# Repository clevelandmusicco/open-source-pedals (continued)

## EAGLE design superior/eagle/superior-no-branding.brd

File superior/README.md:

# Superior Overdrive

The [Superior Overdrive](https://clevelandmusicco.com/pedals/superior-overdrive/) is a 2-in-1 powerhouse pedal packed with our EastSide Overdrive stacked into the WestSide Overdrive. This combination of transparent low- and medium-gain drives, with all their tone and clipping options, is a remarkably flexible dirt platform.

There are 3 interdependent PCBs in this pedal's design.

## The Effect PCB

[Tayda Enclosure Drill Template](https://drill.taydakits.com/box-designs/new?public_key=SVhxKzdDNXZjeXVUNXpSM1phNTFkdz09Cg==)

### Through-hole Component Suggestions

Coming soon.

## The I/O PCB

Coming soon.

## The Filtering & Switching PCB

Coming soon.

## Marketing blurb from our official web site

### A space-saving, rugged, and enormously versatile overdrive platform at an affordable price.

The Cleveland Music Co. Superior Overdrive is a 2-in-1 pedal packed with 2 of our most popular overdrives, and they happen to stack extremely well. Use them individually, set them both to detonate, or dial one in as a boost to help you cut through the mix. These two circuits stacked like this is just glorious; better than any other combination we’ve played. That’s why it’s called the Superior Overdrive.

#### EastSide Overdrive (first in the signal chain)
The Cleveland Music Co. EastSide Overdrive is our love letter to the pinnacle of transparent, boutique overdrives: the Timmy. Its low- to medium-gain tones can be dialed in for anything from a powerful, dirty boost for stacking with other pedals, to flat out rock-n-roll grind. With a potent EQ section and plenty of output volume to spare, the EastSide can easily push an on-the-edge amplifier’s tubes into overdrive territory.

* **VOLUME:** Sets the overall output volume. There is quite a lot of output on tap, which makes the EastSide a great boost option for stacking with other overdrives, or slamming the front of your favorite tube amp.
* **GAIN:** Clockwise for more gain; counter-clockwise for less. While there is a little more gain available than typical transparent overdrives, the EastSide is still a medium-gain pedal. Pro tip: putting a boost or another drive in front of the EastSide can push it into high-gain bliss!
* **TREBLE:** Works like you would expect: adds or cuts treble. Clockwise for more; counter-clockwise for less.
* **BASS:** Adds or cuts bass. Clockwise for more; counter-clockwise for less.
* **COMP | SYM | ASYM:** Selects between three clipping options:
 * Compressed aggressively clips the signal, producing a rich, saturated overdrive tone. This is the least transparent setting.
 * Symmetrical clips the peaks and valleys of the signal equally, resulting in a smooth, sustained overdrive tone.
 * Asymmetrical clips the waveform unequally, creating a more open tone.

The EastSide features an internal trimmer that allows you to fine-tune the bass frequencies prior to the distortion stage of the circuit. Great for “hot” humbuckers that tend to overpower typical overdrives.

#### WestSide Overdrive (second in the signal chain)

The Cleveland Music Co. WestSide Overdrive is inspired by the classic Blues Breaker—both the amp and the pedal. After poring over the schematics of the original JTM 45 amplifier, the original pedal, and many pedals based on both, we applied what we feel are the strengths of them all into the WestSide. Not content to be a rehash of the past, the WestSide offers additional tonal and clipping options, increased output volume, and the powerful presence control makes it feel at home in any rig. The result is a touch-sensitive, bluesy, low-gain overdrive that stacks especially well with our other low- to medium-gain drives, and gives you all the presence you need to stand out.

* **VOLUME:** Sets the overall output volume. Unity gain is around 2 o’clock, so the classic “low-gain, high-volume” configuration can really push the front of a tube amp with the volume cranked.
* **GAIN:** Clockwise for more gain; counter-clockwise for less. There is a little more gain available than from typical pedals of this style, so be brave and explore. But for those looking for the so-called traditional sweet spots, try the 9 o’clock to noon range.
* **PRESENCE:** Sets the amount of Presence. Fully counter-clockwise for most rigs (start here!); clockwise to brighten up a dark amp or guitar pickups.
* **TONE:** Clockwise for more treble; counter-clockwise for less.
* **COMP | OPEN:**
 * Compressed is the traditional clipping option for this style pedal, producing a rich, saturated overdrive tone.
 * Open inserts LEDs as the clipping diodes, resulting in a brighter, louder, and more open sound.

True-bypass switching. Jacks and power are on the top to save space on your pedalboard, and the pedal is industry-standard 1590BB size (4.7 in x 3.7 in x 2.5 in, including knobs).

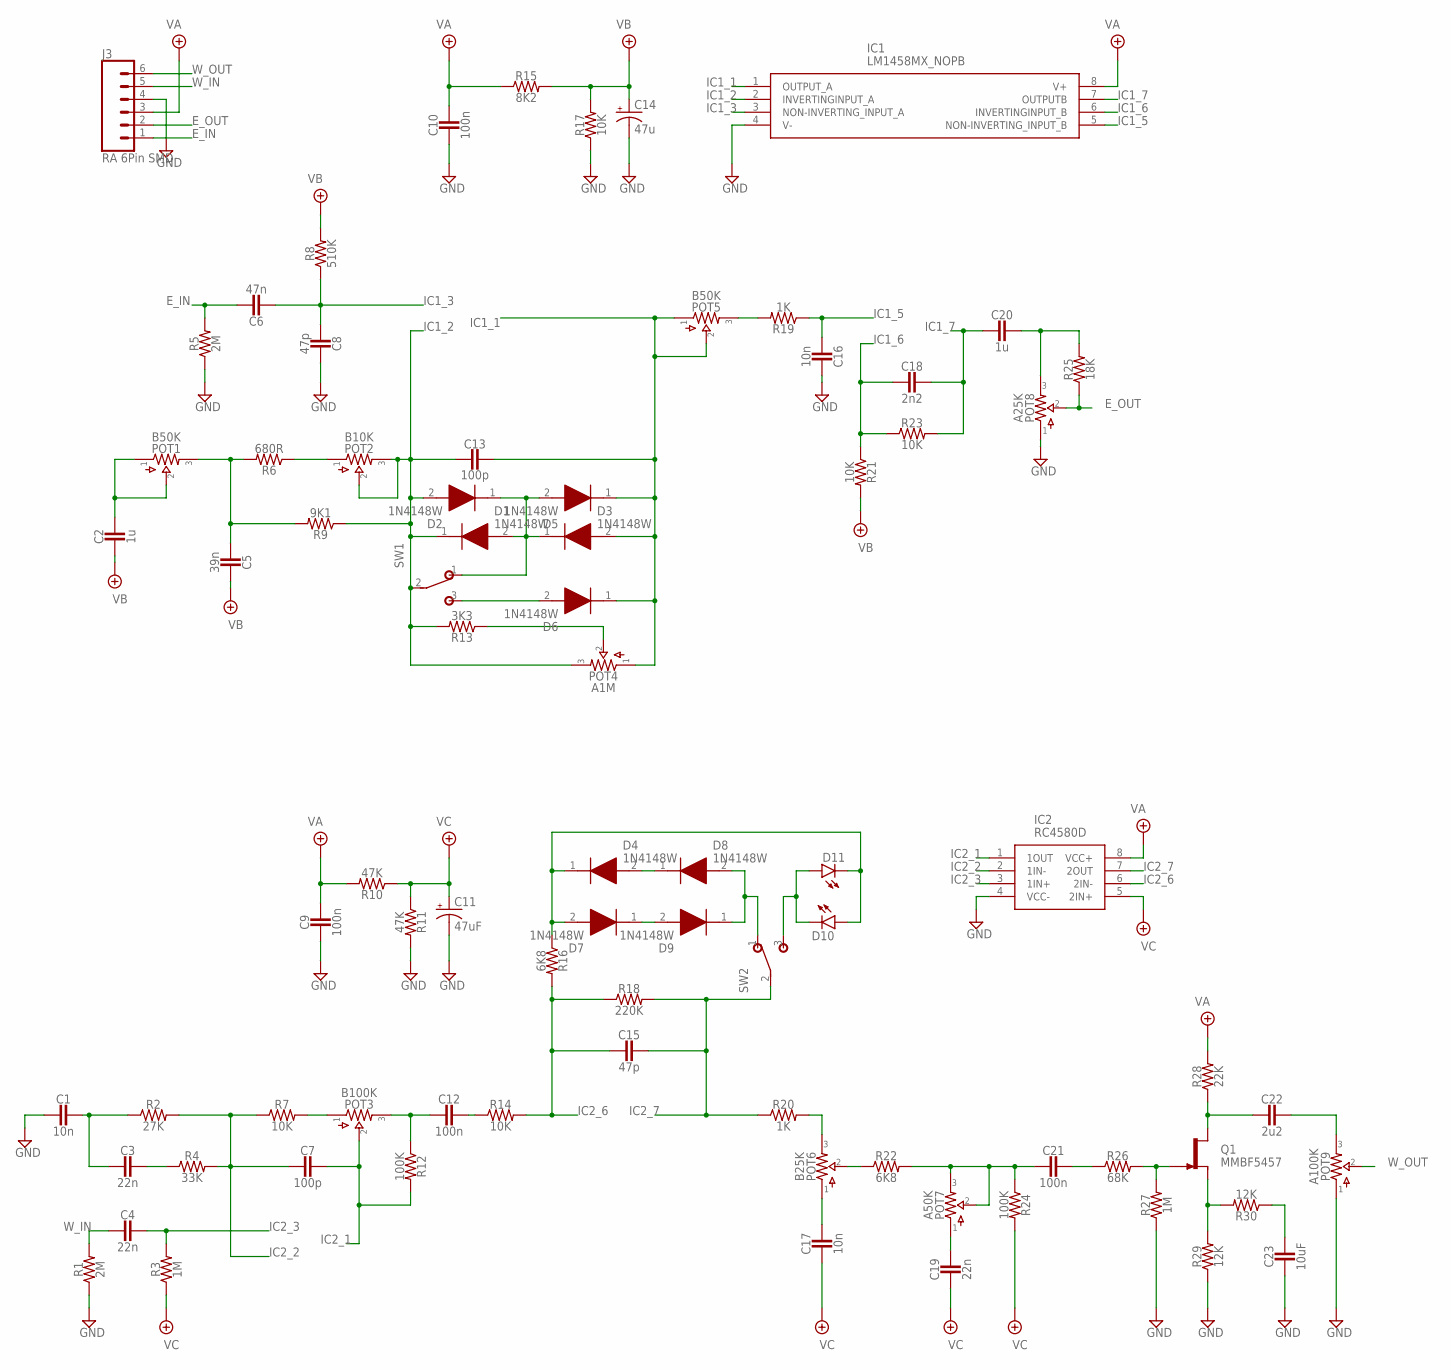
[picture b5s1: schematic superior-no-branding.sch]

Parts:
C1, C16, C17: 10n; 0603
C2: 1u; 0805
C3, C19: 22n; 0603
C4: 22n; 0805
C5: 39n; 0603
C6: 47n; 1206
C7: 100p; 0603
C8, C15: 47p; 0603
C9, C10: 100n; 0603
C11: 47uF; 050_020_1
C12, C21: 100n; 1206
C13: 100p; 0.2".MED
C14: 47u; 050_020_1
C18: 2n2; 0603
C20: 1u; 1206
C22: 2u2; 1206
C23: 10uF; 1206
D1, D2, D3, D4, D5, D6, D7, D8, D9: 1N4148W; SODFL3816X120N
D10, D11: LED3MM
IC1: LM1458MX_NOPB; SOIC127P600X175-8N
IC2: RC4580D; SOIC127P600X175-8N
J3: RA 6Pin SMD; 1X06
POT1, POT5: B50K; 16MM_B.MOUNT
POT2: B10K; TRIM1
POT3: B100K; 16MM_B.MOUNT
POT4: A1M; 16MM_B.MOUNT
POT6: B25K; 16MM_B.MOUNT
POT7: A50K; 16MM_B.MOUNT
POT8: A25K; 16MM_B.MOUNT
POT9: A100K; 16MM_B.MOUNT
Q1: MMBF5457; SOT23-DGS
R1, R5: 2M; 0603
R2: 27K; 0603
R3, R27: 1M; 0603
R4: 33K; 0603
R6: 680R; 0603
R7, R14, R17, R21, R23: 10K; 0603
R8: 510K; 0603
R9: 9K1; 0603
R10, R11: 47K; 0603
R12, R24: 100K; 0603
R13: 3K3; 0603
R15: 8K2; 0603
R16, R22: 6K8; 0603
R18: 220K; 0603
R19, R20: 1K; 0603
R25: 18K; 0603
R26: 68K; 0603
R28: 22K; 0603
R29, R30: 12K; 0603
SW1, SW2: SPDT; M9040P

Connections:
E_IN: C6.1, J3.1, R5.2
E_OUT: J3.2, POT8.2, R25.1
GND: C1.2, C8.1, C9.2, C10.2, C11.-, C14.-, C16.1, C23.2, IC1.4 (V-), IC2.4 (VCC-), J3.4, POT8.1, POT9.1, R1.1, R5.1, R11.2, R17.1, R27.1, R29.1
IC1_1: C13.1, D3.2 (A), D5.1 (K), D6.1 (K), IC1.1 (OUTPUT_A), POT4.1, POT5.1, POT5.2
IC1_2: C13.2, D1.1 (K), D2.2 (A), IC1.2 (INVERTINGINPUT_A), POT2.2, POT2.3, POT4.3, R9.1, R13.2, SW1.2
IC1_3: C6.2, C8.2, IC1.3 (NON-INVERTING_INPUT_A), R8.1
IC1_5: C16.2, IC1.5 (NON-INVERTING_INPUT_B), R19.1
IC1_6: C18.2, IC1.6 (INVERTINGINPUT_B), R21.1, R23.1
IC1_7: C18.1, C20.2, IC1.7 (OUTPUTB), R23.2
IC2_1: C7.1, IC2.1 (1OUT), POT3.2, R12.2
IC2_2: C7.2, IC2.2 (1IN-), R2.2, R4.2, R7.1
IC2_3: C4.1, IC2.3 (1IN+), R3.2
IC2_6: C15.2, IC2.6 (2IN-), R14.2, R16.2, R18.1
IC2_7: C15.1, IC2.7 (2OUT), R18.2, R20.1, SW2.2
unnamed: C5.2, POT1.3, R6.2, R9.2
unnamed: POT4.2, R13.1
unnamed: C2.1, POT1.1, POT1.2
unnamed: POT2.1, R6.1
unnamed: D1.2 (A), D2.1 (K), D3.1 (K), D5.2 (A), SW1.1 (O)
unnamed: D6.2 (A), SW1.3 (S)
unnamed: C3.1, R4.1
unnamed: POT5.3, R19.2
unnamed: C1.1, C3.2, R2.1
unnamed: C12.2, POT3.3, R12.1
unnamed: C20.1, POT8.3, R25.2
unnamed: C12.1, R14.1
unnamed: D4.1 (K), D7.2 (A), D10.A, D11.K (C), R16.1
unnamed: D4.2 (A), D8.1 (K)
unnamed: D7.1 (K), D9.2 (A)
unnamed: POT6.3, R20.2
unnamed: POT6.2, R22.1
unnamed: C17.1, POT6.1
unnamed: C21.2, POT7.2, POT7.3, R22.2, R24.1
unnamed: C21.1, R26.1
unnamed: Q1.G, R26.2, R27.2
unnamed: Q1.S, R29.2, R30.2
unnamed: C23.1, R30.1
unnamed: C22.2, Q1.D, R28.1
unnamed: C22.1, POT9.3
unnamed: D8.2 (A), D9.1 (K), SW2.1 (O)
unnamed: D10.K (C), D11.A, SW2.3 (S)
unnamed: C19.1, POT7.1
unnamed: POT3.1, R7.2
VA: C9.1, C10.1, IC1.8 (V+), IC2.8 (VCC+), J3.3, R10.2, R15.1, R28.2
VB: C2.2, C5.1, C14.+, R8.2, R15.2, R17.2, R21.2
VC: C11.+, C17.2, C19.2, IC2.5 (2IN+), R3.1, R10.1, R11.1, R24.2
W_IN: C4.2, J3.5, R1.2
W_OUT: J3.6, POT9.2

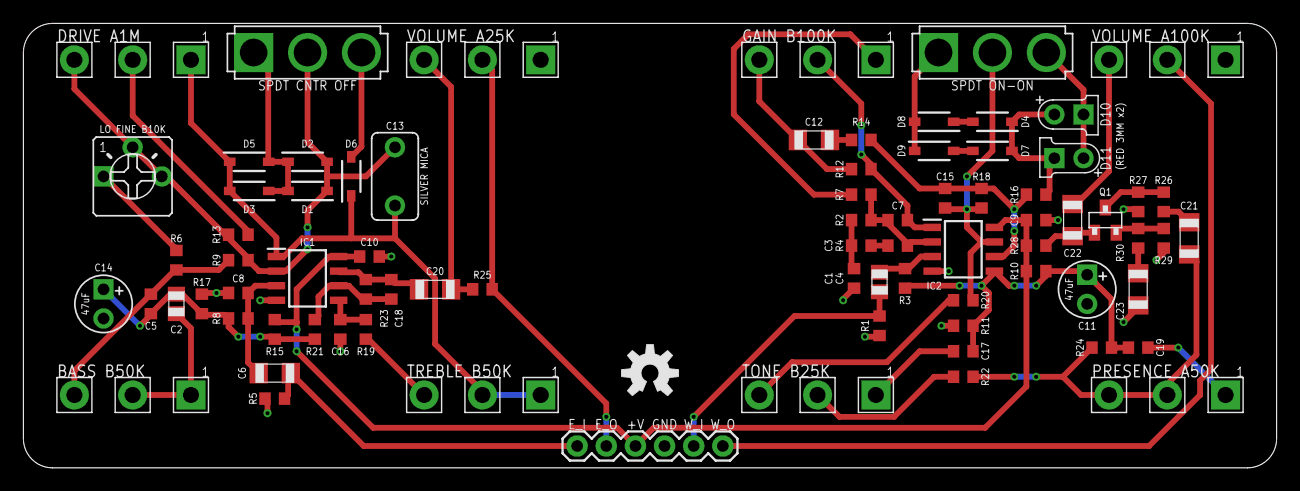
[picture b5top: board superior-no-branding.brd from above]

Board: 2 copper layers, 109.2 x 38.7 mm, 80 parts (0 on the bottom side), 48 nets.

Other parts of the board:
U$3: OSHW-LOGO-M

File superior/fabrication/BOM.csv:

Comment,Designator,Footprint,JLCPCB Part#(optional)
10n,C1,0603,C85973
1u,C2,0805,C28323
22n,C3,0603,C21122
22n,C4,0805,C77069
39n,C5,0603,C107091
47n,C6,1206,C21812
100p,C7,0603,C14858
47p,C8,0603,C1671
100n,C9,0603,C14663
100n,C10,0603,C14663
100n,C12,1206,C97946
47p,C15,0603,C1671
10n,C16,0603,C85973
10n,C17,0603,C85973
2n2,C18,0603,C77033
22n,C19,0603,C21122
1u,C20,1206,C13832
100n,C21,1206,C97946
2u2,C22,1206,C50254
10uF,C23,1206,C14860
1N4148W,D1,SODFL3816X120N,C81598
1N4148W,D2,SODFL3816X120N,C81598
1N4148W,D3,SODFL3816X120N,C81598
1N4148W,D4,SODFL3816X120N,C81598
1N4148W,D5,SODFL3816X120N,C81598
1N4148W,D6,SODFL3816X120N,C81598
1N4148W,D7,SODFL3816X120N,C81598
1N4148W,D8,SODFL3816X120N,C81598
1N4148W,D9,SODFL3816X120N,C81598
LM1458MX_NOPB,IC1,SOIC127P600X175-8N,C444394
RC4580,IC2,SOIC127P600X175-8N,C434475
MMBF5457,Q1,SOT23-DGS,C2830807
2M,R1,0603,C22976
27K,R2,0603,C22967
1M,R3,0603,C22935
33K,R4,0603,C4216
2M,R5,0603,C22976
680R,R6,0603,C23228
10K,R7,0603,C25804
510K,R8,0603,C23192
9K1,R9,0603,C23260
47K,R10,0603,C25819
47K,R11,0603,C25819
100K,R12,0603,C25803
3K3,R13,0603,C22978
10K,R14,0603,C25804
8K2,R15,0603,C25981
6K8,R16,0603,C23212
10K,R17,0603,C25804
220K,R18,0603,C22961
1K,R19,0603,C21190
1K,R20,0603,C21190
10K,R21,0603,C25804
6K8,R22,0603,C23212
10K,R23,0603,C25804
100K,R24,0603,C25803
18K,R25,0603,C25810
68K,R26,0603,C23231
1M,R27,0603,C22935
22K,R28,0603,C31850
12K,R29,0603,C22790
12K,R30,0603,C22790

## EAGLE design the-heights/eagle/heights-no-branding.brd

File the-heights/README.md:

# The Heights Dynadrive

[The Heights Dynadrive](https://clevelandmusicco.com/pedals/heights-dynadrive/) is a great-sounding, medium-gain overdrive circuit that some people are saying emulates the tone of legendary Dumble amplifiers.

OK, that was us. We said that.

[Tayda Enclosure Drill Template](https://drill.taydakits.com/box-designs/new?public_key=Q2JnVDRZVUdWM0dzUno1N0ZWMnJXdz09Cg==)

## Through-hole Component Suggestions

* **C4** - 100uF Low-ESR, 6.3mm diameter, 2.5 mm lead spacing, 0.1" pad spacing @ 25V minimum
* **C6** - 47uF Low-ESR, 5mm diameter, 2mm lead spacing, 0.1" pad spacing @ 25V minimum
* **Potentiometers** - [These](https://lovemyswitches.com/16mm-potentiometers-1-4-smooth-shaft-right-angle-pcb-mount/) work well.

## Optional but nice
* **Dust Seal/Pot "condoms"** - Try [these](https://www.taydaelectronics.com/dust-seal-covers-for-potentiometer.html) for the TONE and VOICE controls to keep the pots from shorting out on the back of the PCB. Or, just cover the pot backs with electrical tape or another insulator.
* **Ribbon cables** - the hook-up wire pads are spaced perfectly for ***pre-bond*** ribbons like [these](https://stompboxparts.com/cables-wire-plugs/ribbon-cable-6-pin-2-prebond/).

## Marketing blurb from our official web site

### The sound and feel of the near-mythical Dumble amplifiers in an affordable pedal.
The Cleveland Music Co. Heights Dynadrive is our tribute to the timeless Zendrive. While it’s a favorite of Blues guitarists, it also makes a great medium-gain rock-n-roll overdrive with a highly dynamic touch. And if that weren’t enough, the Heights stacks really, really well with many other drive pedals; try it before or after a Timmy-like pedal (such as our [EastSide Overdrive](https://clevelandmusicco.com/pedals/eastside-overdrive/)).

#### Controls
* **VOLUME:** Sets the overall output level. There is quite a lot of output on tap, which makes the Heights a great boost option for stacking with other overdrives, or slamming the front of your favorite tube amp.
* **GAIN:** Clockwise for more gain; counter-clockwise for less. The VOICE control interacts with the GAIN control, altering the available gain range. _Pro tip: putting a boost or another drive in front of the Heights can push it even further into pleasing high-gain mayhem!_
* **VOICE:** Alters the available gain as well as bass frequencies in the gain stage. Clockwise for more; counter-clockwise for less. Experiment with the interactivity of the VOICE and GAIN controls; there are many sweet spots hidden in there!
* **TONE:** A simple treble-rolloff. Clockwise for more apparent treble; counter-clockwise for less.

The pedal is housed in an industry standard size 125B aluminum enclosure with jacks and power on the top to help save space on your pedalboard.

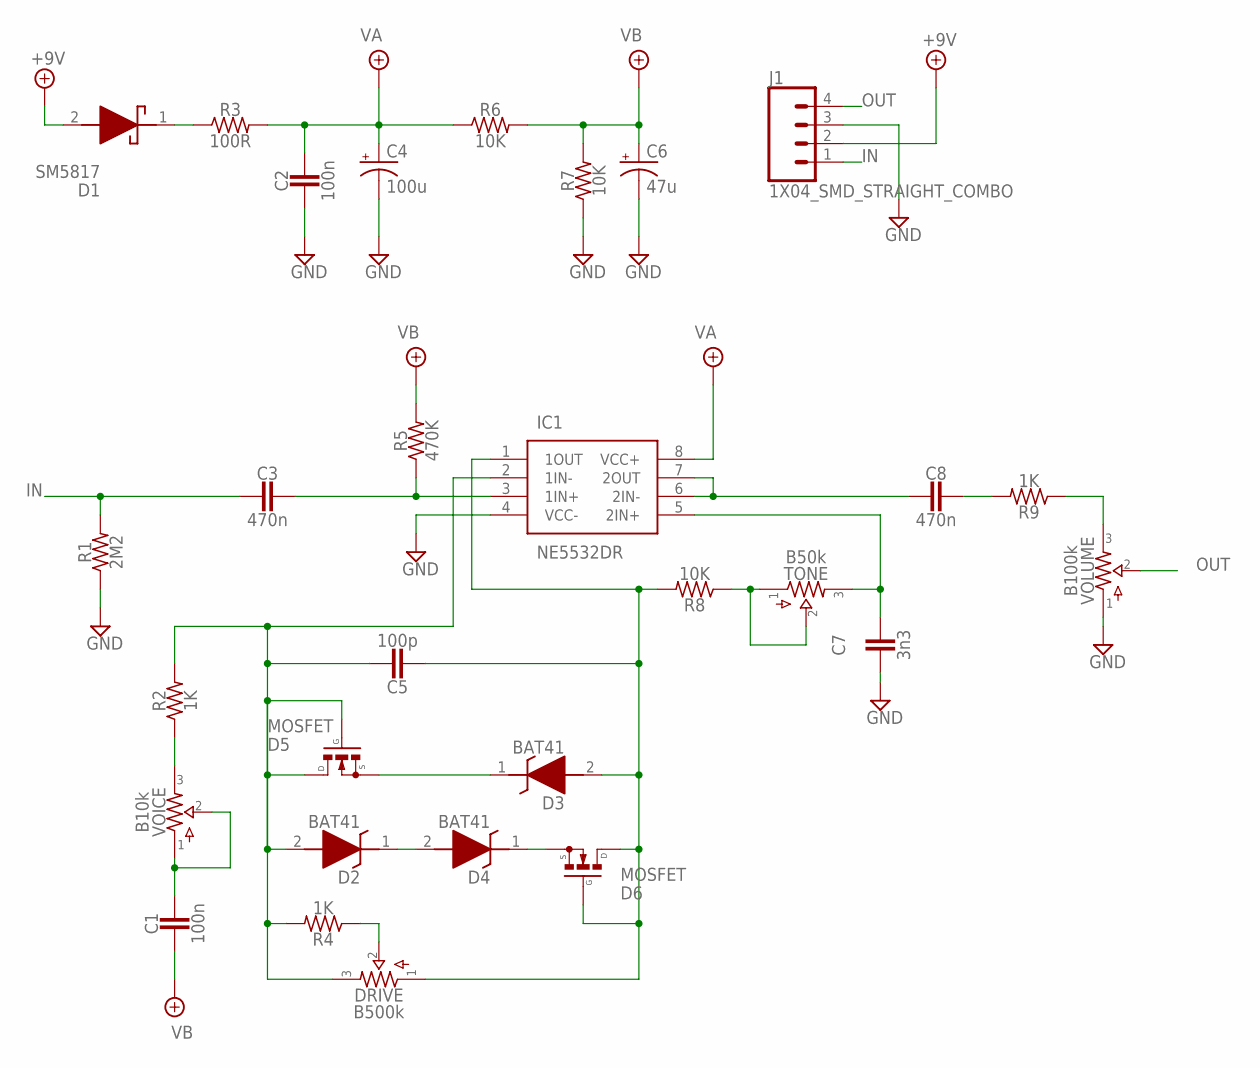
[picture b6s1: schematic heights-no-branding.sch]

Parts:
C1: 100n; RESISTOR_C1206
C2: 100n; RESISTOR_R0603
C3, C8: 470n; RESISTOR_C1206
C4: 100u; 063_025
C5: 100p; RESISTOR_R0603
C6: 47u; 050_020_1
C7: 3n3; RESISTOR_R0603
D1: SM5817; SOD3716X120N
D2, D3, D4: BAT41; SODFL3718X130N
D5, D6: MOSFET; TRANSISTOR_SOT23-GDS
DRIVE: B500k; 16MM_B.MOUNT
IC1: NE5532DR; SOIC127P600X175-8N
J1: 1X04_SMD_STRAIGHT_COMBO; 1X04
R1: 2M2; RESISTOR_R0603
R2, R4, R9: 1K; RESISTOR_R0603
R3: 100R; RESISTOR_R0603
R5: 470K; RESISTOR_R0603
R6, R7, R8: 10K; RESISTOR_R0603
TONE: B50k; 16MM_B.MOUNT
VOICE: B10k; 16MM_B.MOUNT
VOLUME: B100k; 16MM_B.MOUNT

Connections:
+9V: D1.2 (A), J1.2
GND: C2.2, C4.-, C6.-, C7.2, IC1.4 (VCC-), J1.3, R1.1, R7.1, VOLUME.1
IN: C3.2, J1.1, R1.2
unnamed: D1.1 (K), R3.1
unnamed: D2.1 (K), D4.2 (A)
unnamed: C3.1, IC1.3 (1IN+), R5.1
unnamed: C5.1, D2.2 (A), D5.D, D5.G, DRIVE.3, IC1.2 (1IN-), R2.2, R4.2
unnamed: R2.1, VOICE.3
unnamed: C1.1, VOICE.1, VOICE.2
unnamed: DRIVE.2, R4.1
unnamed: C5.2, D3.2 (A), D6.D, D6.G, DRIVE.1, IC1.1 (1OUT), R8.2
unnamed: D3.1 (K), D5.S
unnamed: D4.1 (K), D6.S
unnamed: R8.1, TONE.1, TONE.2
unnamed: C7.1, IC1.5 (2IN+), TONE.3
unnamed: C8.2, IC1.6 (2IN-), IC1.7 (2OUT)
unnamed: C8.1, R9.2
unnamed: R9.1, VOLUME.3
OUT: J1.4, VOLUME.2
VA: C2.1, C4.+, IC1.8 (VCC+), R3.2, R6.1
VB: C1.2, C6.+, R5.2, R6.2, R7.2

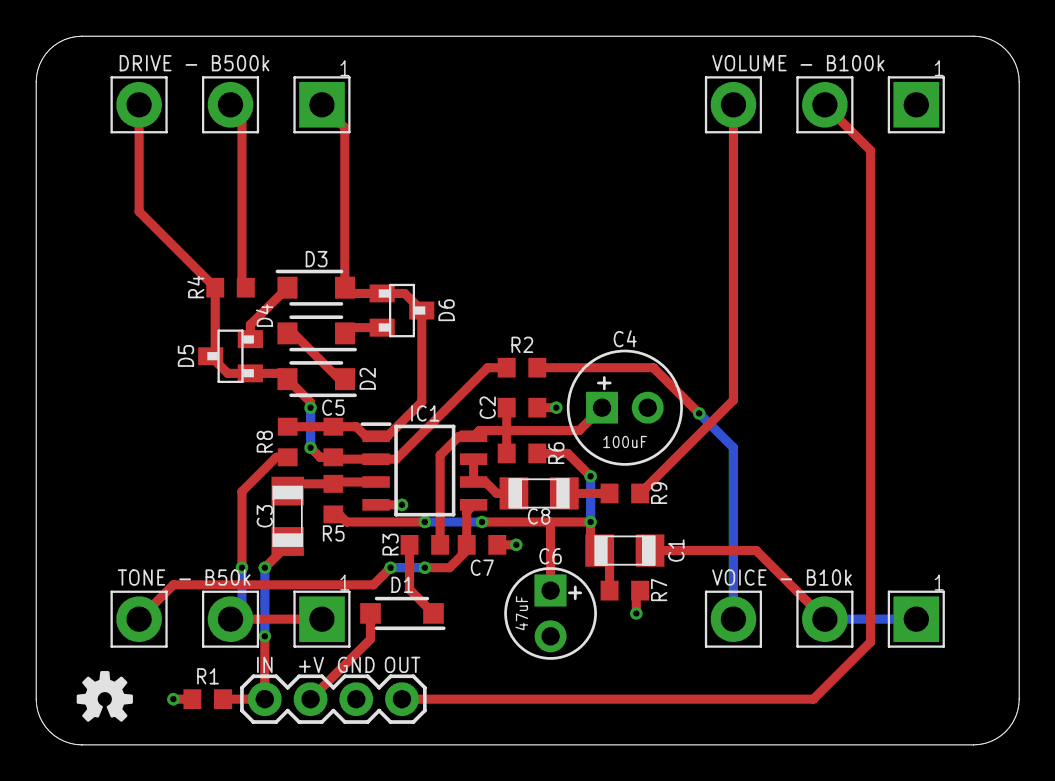
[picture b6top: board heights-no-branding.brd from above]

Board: 2 copper layers, 54.6 x 39.4 mm, 30 parts (0 on the bottom side), 21 nets.

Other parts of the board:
U$2: OSHW-LOGO-S

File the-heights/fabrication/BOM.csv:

Comment,Designator,Footprint,JLCPCB Part #（optional）
100nF,C1,1206,C97946
100nF,C2,0603,C14663
470n,"C3,C8",1206,C6049896
100p,C5,0603,C14858
3n3,C7,0603,C77036
SM5817,D1,SOD3716X120N,C7420328
BAT41,"D2,D3,D4",SOD3816X145N,C222251
MOSFET,"D5,D6",TRANSISTOR_SOT23-GDS,C20917
NE5532DR,IC1,SOIC127P600X175-8N,C7426
2M,R1,0603,C22976
1K,"R2,R4,R9",0603,C21190
100R,R3,0603,C22775
470K,R5,0603,C23178
10K,"R6,R7,R8",0603,C25804

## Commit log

2025-07-26 Add Superior (partial)
2025-12-27 Add preliminary Hothouse structure
2025-12-27 Enhance README with overview and resource links
    Updated the README to include an overview section and formatted the resources table with clickable links for sourcing components.
2025-12-27 Add drill template and refine README
2025-12-27 Enhance README with links and formatting updates
    Updated README to include links and improve clarity.
2025-12-27 Update README with PCB images and descriptions
    Added images and descriptions for the main PCB and daughterboards.
2025-12-27 Revise BOM with component availability details
    Updated the Bill of Materials section to clarify component availability and added notes on substitutions.
2025-12-28 Add Eagle files and refine README
2025-12-28 Add Hothouse schematic PDFs
2025-12-31 Revise README for Hothouse DSP Pedal Kit
    Updated README to clarify product name and details.
2025-12-31 Add .csv versions of Hothouse BOM and CPL files
2025-12-31 Revise README for Hothouse DSP Pedal Kit
    Updated README to reflect the correct product name and improve clarity in descriptions. Removed redundant sentences and ensured consistency in language throughout the document.
2026-01-02 Add initial files for The 'Why'
2026-01-02 Fix formatting and clarify SMT project description
    Corrected formatting and improved clarity in the text regarding SMT components and project intent.
2026-01-02 Revise README.md for clarity and consistency
    Updated the README.md to improve clarity and consistency in language regarding the Big Muff circuit variations, BOM usage, and SMT components.
2026-01-02 Refine README with additional details and clarity
    Updated README.md for clarity and added details about BOMs and capacitor footprints.
